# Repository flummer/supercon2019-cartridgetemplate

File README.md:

# Unofficial KiCad template for a 2019 Hackaday Superconference Badge Cartridge

This template can be used as a starting point to make a cartridge for the Supercon badge, that will mate with the 40 pin expansion connector on the back of the badge.

| WARNING: This design is unofficial, and has NOT been tested |
| --- |

It's using an angled 2x20 pin male header, a w25q128 SPI flash and a 100nF cap. The schematic has the pins named using global nets, so it's easy to simply add in your own stuff.

## Version 1.2 update

This updated version fixes an error in the pin connections on the cartridge connector (the two columns was flipped for some signals) and adds a copper pour (connected to GND) on the bottom layer too.

## Special note about the original version

If you want to use a PCB based on the original version with incorrect connections, it is possible to make a hardware hack on the 20x2 angeled header, where you move the pins around and bend some of them a bit, very precisely.

## License

The contents of this repository is released under the following licence:

 * the "Creative Commons Attribution-ShareAlike 4.0 International License"
   (CC BY-SA 4.0) full text of this license is included in the LICENSE file
   and a copy can also be found at
   http://creativecommons.org/licenses/by-sa/4.0/

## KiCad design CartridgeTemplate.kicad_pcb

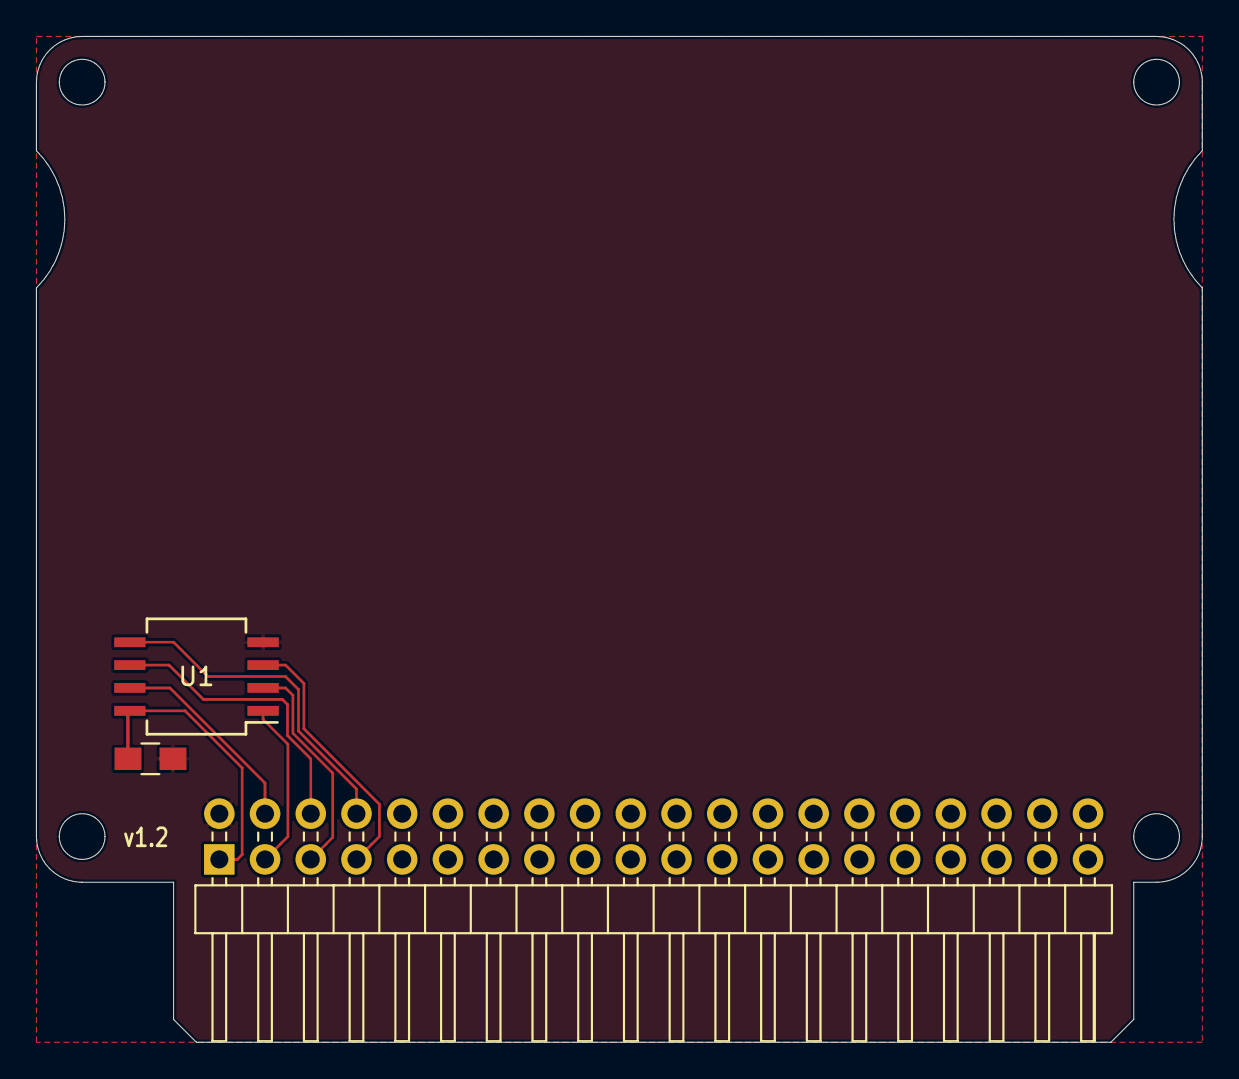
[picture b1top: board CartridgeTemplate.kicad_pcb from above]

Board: 2 copper layers, 64.8 x 55.9 mm, 3 parts (0 on the bottom side), 8 nets.

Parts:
C1: 100nF; C_0805_HandSoldering
J1: Cartridge Connector; Supercon_Cartridge_40pin_Connector
U1: W25Q128; SO-8_5.3x6.2mm_Pitch1.27mm

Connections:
+3V3: C1.1, J1.1, U1.8
F_CS: J1.3, U1.1
F_HOLD: J1.4, U1.7
F_MISO: J1.5, U1.2
F_MOSI: J1.8, U1.5
F_SCK: J1.6, U1.6
F_WP: J1.7, U1.3
GND: C1.2, J1.2, U1.4

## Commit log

2019-10-08 Initial commit
    Initial version of the template, should work, but has NOT been tested with actual hardware
2019-10-08 Added readme
2019-10-13 Added LICENSE file
2019-10-16 Added badge outline in Dwgs.Use
    This is not the exact outline, but a guess based on the official proto breakout cartridge and a photo of a badge
2019-10-16 Updated README with render
2019-10-25 Moved auxillary axis origin to make more sense
2019-10-26 Removed library reference that is not needed
2019-10-26 Updated .gitignore
2019-11-16 Fixed error in cartridge connector pin assignments
    Also added copper pour on bottom layer
    Updated to version 1.2
